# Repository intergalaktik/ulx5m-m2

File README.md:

# Work in progress!!! 

# ULX5M-M2
GateMate FPGA on M2 card

## Blinky

## SerDes test 

For initial test of V0.1 SerDes We have used messy setup.
On CM5 BaseBoard we have our ULX5M-GS board, and on M2 HAT we have M2 v0.1 board
PCIe lines are connected with small cable.
We have successfull data transfer and 1.25Gbit/s is without errors
2.5G is with some filter adjustment (v0.2) in good shape - almost without errors so usable!
We did not manage to get higher that 2.5G connections between v005 GS and M2 v0.1

#### ULX5M-M2 V001

- [x] JTAG 
- [x] FLASH
- [x] LEDs
- [x] Blinkey
- [x] USB - device shows up
- [] BTNS
- [] SDRAM
- [x] SerDes with connection to ULX5M-GS - low speed 1.25Gbit/s SerDes transfer.
- [] PCIe

#### ULX5M-M2 V002 - ordered

- [] JTAG 
- [] FLASH
- [] LEDs
- [] Blinkey
- [] USB - device shows up
- [] BTNS
- [] SDRAM
- [] SerDes with connection to ULX5M-GS I am getting low speed SerDes transfer.
- [] PCIe

## References

https://github.com/intergalaktik/ulx5m-gs

https://github.com/OLIMEX/GateMateA1-EVB

https://github.com/intergalaktik/Extension_Boards_for_Olimex_GateMate

https://github.com/YosysHQ/prjpeppercorn-test-cases

https://github.com/YosysHQ/prjpeppercorn
  
https://github.com/chili-chips-ba/openCologne

https://www.chili-chips.xyz/open-cologne

## Acknowledgements

This project was done in collaboration with Chili Chips*Ba team. 
They have put enormes effort in making all cores to work on GateMate even before we have our own board!
Thanks to them now we have big set of cores that can be used to check and improve opensource toolchain!
They are proven to be reliable partners that solves problem quickly and on side works on educating younger generations!
Also big thanks goes to YosysHQ as they are doing miracles with open source tooling, and we now finaly have one that works for GateMate!
From YosysHQ special thanks to Micko and Lofty that are helping in real time on Discord!
Special thanks to Patrick from Cologne, as without him and rest of Cologne team we would not be able to get this project done.

## Work on this board is financed by NLnet foundation

https://nlnet.nl/project/openCologne/

https://nlnet.nl/project/OpenCologne-PCIe/

https://github.com/chili-chips-ba/openCologne-PCIE

This project was funded through the NGI0 Commons Fund, a fund established by NLnet with financial support from the European Commission's Next Generation Internet programme, under the aegis of DG Communications Networks, Content and Technology under grant agreement No 101135429. Additional funding is made available by the Swiss State Secretariat for Education, Research and Innovation (SERI).

## Check up our blogposts
Comming soon!!!

## Contact us

Discord: https://discord.gg/qwMUk6W

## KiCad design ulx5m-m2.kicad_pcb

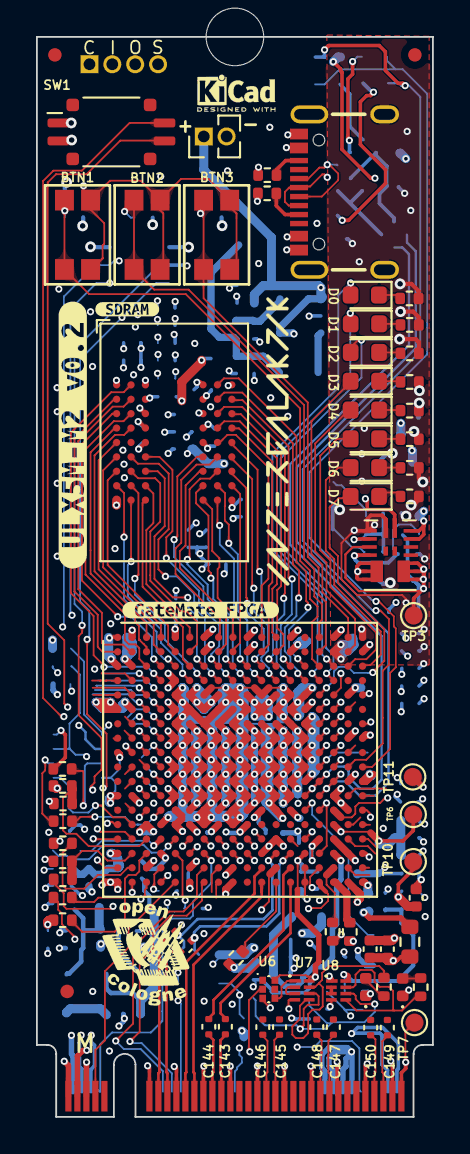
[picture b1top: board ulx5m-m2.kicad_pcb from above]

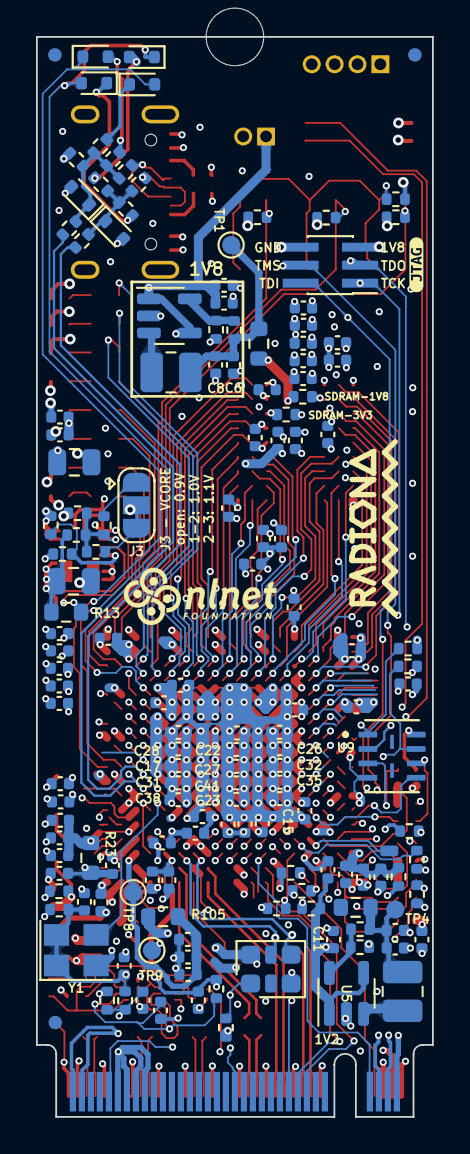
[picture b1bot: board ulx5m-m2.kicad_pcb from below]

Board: 6 copper layers, 22.0 x 60.0 mm, 231 parts (156 on the bottom side), 157 nets.

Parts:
BTN1, BTN2, BTN3: SW_Push; Switch_EVPAA
C1, C10: 22u; C_0805_2012Metric
C2, C11: 4u7; C_0402_1005Metric
C4, C15, C18, C23, C28, C32, C35, C38, C41, C126: 10n; C_0402_1005Metric
C6, C24: 10u; C_0402_1005Metric
C8, C29: 1u; C_0402_1005Metric
C13, C16, C21, C26, C36, C44, C51, C54, C75, C78, C86, C90, C94, C100, C122, C123, C131: 2u2; C_0402_1005Metric
C14, C17, C22, C27, C31, C34, C37, C40, C42, C45, C47, C48, C49, C52, C55, C56, C57, C76, C79, C80, C88, C89, C92, C93, C96, C97, C102, C103, C127, C128, C132, C133, C138: 100n; C_0402_1005Metric
C33, C87, C91, C95, C120, C121: 220n; C_0402_1005Metric
C39, C43, C50, C53, C58, C77, C98, C124, C125: 22u; C_0402_1005Metric
C85: 2.2uF; C_0402_1005Metric
C99, C101, C140, C141: 22nF; C_0402_1005Metric
C136, C137: 100n; C_0402_SI_M
C143, C144, C145, C146, C147, C148, C149, C150: 220nF; C_0402_SI_M
D1: green; D_0402_1005Metric
D2: red; D_0402_1005Metric
D3, D4: 3.6V; D_SOD-523
D5, D6, D7, D8: 1N914; D_SOD-523
D9, D10, D11, D12, D13, D14, D15, D16: LED; LED_0603_1608Metric
FID101, FID102, FID103, FID104, FID105, FID106: Fiducial; Fiducial_0.75mm_Mask1.5mm
H5: MountingHole_Pad; MountingHole_3.2mm_M3
J3: Vcore_sel; SolderJumper-3_P1.3mm_Open_RoundedPad1.0x1.5mm
J4: JTAG; PinHeader_2x03_P1.00mm_Vertical_SMD
J5: USB_C_Receptacle; USB-C_16
J10: M.2 M Key Connector
J101: JTAG_EXT; PinHeader_1x04_P1.27mm_Vertical
J102: 3V3_PSU; PinHeader_1x02_P1.27mm_Vertical
L1, L3: DFE322512F-2R2M=P2; L_1008_2520Metric
LoGo_opencologne: MountingHole; open_cologne_small
R1, R4, R143: 100k; R_0402_1005Metric
R2: 51k; R_0402_1005Metric
R3, R17, R18: 200k; R_0402_1005Metric
R7, R8, R116, R141, R142: 0R; R_0402_1005Metric
R9, R66, R112, R113, R115: dnp; R_0402_1005Metric
R10, R13, R21: 0R; R_0603_1608Metric
R12: 40k; R_0402_1005Metric
R14: 120k; R_0402_1005Metric
R15: 20k; R_0402_1005Metric
R16: 60k; R_0402_1005Metric
R23, R105, R106: 1R; R_0603_1608Metric
R24, R25, R27, R29, R30, R111: 10k; R_0402_1005Metric
R31, R32: 200R; R_0402_1005Metric
R33, R34, R35, R36, R38, R39: 4k7; R_0402_1005Metric
R37, R40, R41, R42, R43: 27R; R_0402_1005Metric
R44, R45: 27; R_0402_1005Metric
R46, R48, R58: 1k; R_0402_1005Metric
R47, R55: 12k1; R_0402_1005Metric
R59, R63, R64, R65, R86, R87, R88, R95, R118: R300; R_0402_1005Metric
R61, R62: 5k1; R_0402_1005Metric
R109: 200; R_0402_1005Metric
R121, R122, R123: 4R7; R_0402_1005Metric
R144, R145, R146: 1K; R_0402_1005Metric
SW1: 219-2MST; SW_DIP_SPSTx02_Slide_Copal_CVS-02xB_W5.9mm_P1mm
TP1: 1V8; TestPoint_Pad_D1.0mm
TP3: Vcore; TestPoint_Pad_D1.0mm
TP4: 1V2; TestPoint_Pad_D1.0mm
TP6: VDD_PLL; TestPoint_Pad_D1.0mm
TP7, TP9, TP11: GND; TestPoint_Pad_D1.0mm
TP8: VDD_SER_PLL; TestPoint_Pad_D1.0mm
TP10: VDD_SER; TestPoint_Pad_D1.0mm
TP12: SPI_FWD; TestPoint_Pad_1.0x1.0mm
U1, U5: TLV62569DBV; SOT-23-5
U3: MPM3833CGRH-Z
U4: GateMate-CCGM1A1; BGA-324_15.0x15.0mm_Layout18x18_P0.8mm_Ball0.45mm_Pad0.4mm_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
U6: 74LVC1G04GM,115; PESD3V3L5UF115
U7, U8: 74LVC2G00HK3-7; 74LVC2G00HK37
U9: AT25QL321-MBUE-T; SON80P400X300X60-10N
U10: IS42S16320D-6BLI
X2: 511FCA100M000BAG; Oscillator_SMD_SiTime_PQFD-6L_3.2x2.5mm
Y1: ASE2-25.000MHZ-L-C-T; Crystal_SMD_TXC_7M-4Pin_3.2x2.5mm
kibuzzard-6A9AE930: G***; kibuzzard-6A9AE930
kibuzzard-686AA7AF: G***; kibuzzard-686AA7AF
kibuzzard-686AA726: G***; kibuzzard-686AA726
kibuzzard-686CE423: G***; kibuzzard-686CE423
radiona: radiona

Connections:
+3V3: C1.1, C2.1, C11.1, C49.1, C85.1, C94.1, C95.1, C96.1, C97.1, C98.1, C99.1, C100.1, C101.1, C102.1, C103.1, C140.1, C141.1, J10.2 (+3.3V), J10.4 (+3.3V), J10.12 (+3.3V), J10.14 (+3.3V), J10.16 (+3.3V), J10.18 (+3.3V), J10.70 (+3.3V), J10.72 (+3.3V), J10.74 (+3.3V), J102.1, R1.1, R58.2, R115.2, R121.1, U1.1 (EN), U1.4 (VIN), U3.13 (IN), U3.14 (IN), U4.A16 (VDD_EB), U4.B18 (VDD_EB), U4.E14 (VDD_EB), U4.E17 (VDD_EB), U4.F13 (VDD_EB), U4.G14 (VDD_EA), U4.H17 (VDD_EA), U4.J14 (VDD_EA), U4.L14 (VDD_EA), U4.L17 (VDD_EA), U5.1 (EN), U5.4 (VIN)
/CLKREQ#: J10.52 (CLKREQ#), U4.V7 (IO_SA_B3)
/DEVSLP: J10.38 (DEVSLP), U4.R7 (IO_SA_A2)
/LED1#: J10.10 (DAS/DSS#/LED1#), U4.T6 (IO_SA_B1)
/M.2 M Key/PCIe_CLK_N: C137.2, J10.53 (REFCLKn)
/M.2 M Key/PCIe_CLK_P: C136.2, J10.55 (REFCLKp)
/M.2 M Key/PCIe_RX_N: J10.47 (PERn0/SATA-A-), U4.V11 (SER_RX_N)
/M.2 M Key/PCIe_RX_P: J10.49 (PERp0/SATA-A+), U4.U11 (SER_RX_P)
/M.2 M Key/PCIe_TX_N: C143.2, U4.V13 (SER_TX_N)
/M.2 M Key/PCIe_TX_P: C144.2, U4.U13 (SER_TX_P)
/M.2 M Key/PET0N: C143.1, J10.41 (PETn0/SATA-B+)
/M.2 M Key/PET0P: C144.1, J10.43 (PETp0/SATA-B-)
/M.2 M Key/PET1N: C145.1, J10.29 (PETn1)
/M.2 M Key/PET1P: C146.1, J10.31 (PETp1)
/M.2 M Key/PET2N: C147.1, J10.17 (PETn2)
/M.2 M Key/PET2P: C148.1, J10.19 (PETp2)
/M.2 M Key/PET3N: C149.1, J10.5 (PETn3)
/M.2 M Key/PET3P: C150.1, J10.7 (PETp3)
/PEDET: J10.69 (PEDET), U4.V5 (IO_SA_B0)
/PERST#: J10.50 (PERST#), U4.R6 (IO_SA_A1)
/PEWAKE#: J10.54 (PEWAKE#), U4.U7 (IO_SA_A3)
/SUSCLK: J10.68 (SUSCLK), U4.T7 (IO_SA_B2)
/config/+1V8_FLASH: C43.1, C44.1, C45.1, R123.1, U4.N5 (VDD_WA), U4.P3 (VDD_WA), U4.P5 (VDD_WA), U4.T1 (VDD_WA), U4.U3 (VDD_WA)
/config/CFG_DONE: U4.V3 (IO_WA_B2/CFG_DONE), U6.2 (A)
/config/JTAG_CFG_MD0: R29.1, U4.R5 (CFG_MD0/IO_WA_A0)
/config/JTAG_CFG_MD1: R27.1, U4.T5 (CFG_MD1/IO_WA_B0)
/config/JTAG_CFG_MD2: R25.1, SW1.4, U4.U4 (CFG_MD2/IO_WA_A1)
/config/JTAG_CFG_MD3: R24.1, SW1.3, U4.V4 (CFG_MD3/IO_WA_B1)
/config/JTAG_POR: R30.1, R66.2, U4.U1 (POR_EN/IO_WA_A3)
/config/JTAG_TCK: R39.1, R40.1, U4.R3 (JTAG_TCK/IO_WA_A5)
/config/JTAG_TDI: R36.2, R41.1, U4.T2 (JTAG_TDI/IO_WA_A4)
/config/JTAG_TDO: R42.1, U4.U2 (JTAG_TDO/IO_WA_B3)
/config/JTAG_TMS: R34.2, R43.1, U4.T3 (JTAG_TMS/IO_WA_B4)
/config/SPI_CSN: R38.2, U4.N3 (IO_WA_A8/~SPI_CS), U9.1 (~CS)
/config/SPI_IO0: U4.P2 (IO_WA_B7/SPI_D0), U9.5 (SI/SIO0)
/config/SPI_IO1: U4.P1 (IO_WA_A7/SPI_D1), U9.2 (SO/SIO1)
/config/SPI_IO2: R35.2, U4.R2 (IO_WA_B6/SPI_D2), U9.3 (~WP/SIO2)
/config/SPI_IO3: R33.2, U4.R1 (IO_WA_A6/SPI_D3), U9.7 (~RESET/SIO3)
/config/SPI_SCK: R37.1, U4.N4 (IO_WA_B8/SPI_CLK)
/config/~CFG_FAIL: U4.V2 (IO_WA_A2/~CFG_FAILED), U8.1 (1A)
/ethernet/ALED0: D9.1 (K), R59.1
/ethernet/ALED1: D10.1 (K), R63.1
/ethernet/ALED2: D11.1 (K), R64.1
/ethernet/ALED3: D12.1 (K), R65.1
/ethernet/ALED4: D13.1 (K), R86.1
/ethernet/ALED5: D14.1 (K), R87.1
/ethernet/ALED6: D15.1 (K), R88.1
/ethernet/ALED7: D16.1 (K), R95.1
/ethernet/BTN1: BTN1.2, R144.2, U4.C15 (IO_EB_B7)
/ethernet/BTN2: BTN2.2, R145.2, U4.A15 (IO_EB_B8)
/ethernet/BTN3: BTN3.2, R146.2, U4.B15 (IO_EB_A8)
/ethernet/FPD1+: J5.A6 (D+), J5.B6 (D+), R45.2
/ethernet/FPD1-: J5.A7 (D-), J5.B7 (D-), R44.2
/ethernet/LED0: D9.2 (A), U4.D15 (IO_EB_A7)
/ethernet/LED1: D10.2 (A), U4.C16 (IO_EB_B6)
/ethernet/LED2: D11.2 (A), U4.D16 (IO_EB_A6)
/ethernet/LED3: D12.2 (A), U4.A17 (IO_EB_B5)
/ethernet/LED4: D13.2 (A), U4.B17 (IO_EB_A5)
/ethernet/LED5: D14.2 (A), U4.C17 (IO_EB_B4)
/ethernet/LED6: D15.2 (A), U4.C18 (IO_EB_A4)
/ethernet/LED7: D16.2 (A), U4.E15 (IO_EB_B3)
/ethernet/USB25_N: R141.1, U4.L15 (IO_EA_B1), U4.M14 (IO_EA_B0)
/ethernet/USB25_P: R142.1, U4.L16 (IO_EA_A1), U4.M15 (IO_EA_A0)
/ethernet/USB_CC1: J5.A5 (CC1), R61.2
/ethernet/USB_CC2: J5.B5 (CC2), R62.2
/ethernet/USB_N: D4.1 (K), R44.1, R48.1, R55.2, R141.2
/ethernet/USB_P: D3.1 (K), R45.1, R46.2, R47.2, R58.1, R142.2
/ethernet/USB_PULL_N: D7.2 (A), D8.1 (K), U4.K17 (IO_EA_B2)
/ethernet/USB_PULL_P: D5.2 (A), D6.1 (K), U4.K18 (IO_EA_A2)
/lvds/+1V8_SB: C53.1, C54.1, C55.1, R122.1, U4.N11 (VDD_SB), U4.N13 (VDD_SB), U4.N18 (VDD_SB), U4.R15 (VDD_SB), U4.T18 (VDD_SB)
/lvds/+3V3_SA: C50.1, C51.1, C52.1, R121.2, U4.P6 (VDD_SA), U4.P8 (VDD_SA), U4.P10 (VDD_SA), U4.U6 (VDD_SA), U4.U9 (VDD_SA)
/lvds/CLK_25MHz: U4.N14 (CLK0/IO_SB_A8), Y1.3
/serdes/SER_CK_N: C137.1, U4.T13 (SER_CLK_N), X2.5 (OUT-)
/serdes/SER_CK_P: C136.1, U4.T12 (SER_CLK), X2.4 (OUT+)
/serdes/SER_PORT_ADJ: C133.1, R112.2, R113.1, U4.V15 (POR_ADJ)
GND: C1.2, C2.2, C4.1, C6.2, C8.2, C10.2, C11.2, C13.2, C14.2, C15.2, C16.2, C17.2, C18.2, C21.2, C22.2, C23.2, C24.2, C26.2, C27.2, C28.2, C29.2, C31.2, C32.2, C33.2, C34.2, C35.2, C36.2, C37.2, C38.2, C39.2, C40.2, C41.2, C42.2, C43.2, C44.2, C45.2, C47.2, C48.2, C49.2, C50.2, C51.2, C52.2, C53.2, C54.2, C55.2, C56.2, C57.2, C58.2, C75.2, C76.2, C77.2, C78.2, C79.2, C80.2, C85.2, C86.2, C87.2, C88.2, C89.2, C90.2, C91.2, C92.2, C93.2, C94.2, C95.2, C96.2, C97.2, C98.2, C99.2, C100.2, C101.2, C102.2, C103.2, C120.2, C121.2, C122.2, C123.2, C124.2, C125.2, C126.2, C127.2, C128.2, C131.2, C132.2, C133.2, C138.2, C140.2, C141.2, D1.1 (K), D2.1 (K), D3.2 (A), D4.2 (A), J3.2, J4.6, J5.GND, J5.NC1 (NC), J5.NC2 (NC), J5.NC3 (NC), J5.S (SHIELD), J10.1 (GND), J10.3 (GND), J10.9 (GND), J10.15 (GND), J10.21 (GND), J10.27 (GND), J10.33 (GND), J10.39 (GND), J10.45 (GND), J10.51 (GND), J10.57 (GND), J10.71 (GND), J10.73 (GND), J10.75 (GND), J102.2, R2.2, R4.2, R7.2, R8.2, R12.1, R18.2, R24.2, R25.2, R27.2, R29.2, R30.2, R39.2, R59.2, R61.1, R62.1, R63.2, R64.2, R65.2, R86.2, R87.2, R88.2, R95.2, R109.1, R113.2, R118.2, TP7.1 (1_1), TP9.1 (1_1), TP11.1 (1_1), U1.2 (GND), U3.1 (AGND), U3.16 (PGND), U4.A1 (GND), U4.A7 (GND), U4.A10 (GND), U4.A13 (GND), U4.A18 (GND), U4.B16 (GND), U4.C1 (GND), U4.E5 (GND), U4.E7 (GND), U4.E9 (GND), U4.E11 (GND), U4.E13 (GND), U4.E18 (GND), U4.F1 (GND), U4.F6 (GND), U4.F8 (GND), U4.F10 (GND), U4.F12 (GND), U4.F14 (GND), U4.G5 (GND), U4.G7 (GND), U4.G9 (GND), U4.G11 (GND), U4.G13 (GND), U4.H6 (GND), U4.H8 (GND), U4.H10 (GND), U4.H12 (GND), U4.H14 (GND), U4.H18 (GND), U4.J1 (GND), U4.J5 (GND), U4.J7 (GND), U4.J9 (GND), U4.J11 (GND), U4.J13 (GND), U4.K6 (GND), U4.K8 (GND), U4.K10 (GND), U4.K12 (GND), U4.K14 (GND), U4.L5 (GND), U4.L7 (GND), U4.L9 (GND), U4.L11 (GND), U4.L13 (GND), U4.L18 (GND), U4.M1 (GND), U4.M6 (GND), U4.M8 (GND), U4.M10 (GND), U4.M12 (GND), U4.M16 (GND), U4.N7 (GND), U4.N9 (GND), U4.N12 (GND), U4.N17 (GND), U4.P4 (GND), U4.P7 (GND), U4.P9 (GND), U4.R12 (GND), U4.R16 (GND), U4.T4 (GND), U4.T11 (GND), U4.T17 (GND), U4.U14 (GND), U4.U15 (GND), U4.V1 (GND), U4.V6 (GND), U4.V9 (GND), U4.V14 (GND), U4.V18 (GND), U5.2 (GND), U6.3 (GND), U7.4 (GND), U8.4 (GND), U9.4 (GND), U10.A1 (VSS), U10.A3 (VSSQ), U10.B7 (VSSQ), U10.C3 (VSSQ), U10.D7 (VSSQ), U10.E3 (VSS), U10.J1 (VSS), X2.3 (GND), Y1.2
unnamed: BTN1.1, BTN2.1, BTN3.1, R118.1
unnamed: C6.1, C8.1, L1.2, R3.1, R10.1, TP1.1 (1_1)
unnamed: C24.1, C29.1, L3.2, R17.1, R21.1, TP4.1 (1_1)
unnamed: D1.2 (A), R31.2
unnamed: D2.2 (A), R32.2
unnamed: D5.1 (K), R46.1
unnamed: D6.2 (A), R47.1
unnamed: D7.1 (K), R48.2
unnamed: D8.2 (A), R55.1
unnamed: J3.1, R14.1
unnamed: J3.3, R16.1
unnamed: J4.1, J101.1, R40.2
unnamed: J4.2, J101.2, R41.2
unnamed: J4.3, J101.3, R42.2
unnamed: J4.4, J101.4, R43.2
unnamed: R7.1, U4.U16 (GND)
unnamed: R8.1, U4.V16 (GND)
unnamed: R3.2, R4.1, U1.5 (FB)
unnamed: L1.1, U1.3 (SW)
unnamed: R1.2, R2.1, U3.4 (EN)
unnamed: R12.2, R14.2, R15.2, R16.2, U3.2 (FB)
unnamed: C10.1, R13.1, R15.1, TP3.1 (1_1), U3.3 (OUT_S), U3.8 (OUT), U3.9 (OUT), U3.10 (OUT)
unnamed: U3.5 (SW), U3.6 (SW), U3.7 (SW), U3.15 (SW)
unnamed: R109.2, U4.V12 (SER_RTERM)
unnamed: TP12.1 (1_1), U4.R4 (IO_WA_B5/SPI_FWD)
unnamed: R9.1, U4.N16 (NC)
unnamed: R17.2, R18.1, U5.5 (FB)
unnamed: L3.1, U5.3 (SW)
unnamed: U6.4 (Y), U7.1 (1A)
unnamed: U7.2 (1B), U7.3 (2Y)
unnamed: R31.1, U7.5 (2A), U7.7 (1Y)
unnamed: U8.2 (1B), U8.3 (2Y)
unnamed: R32.1, U8.5 (2A), U8.7 (1Y)
unnamed: R37.2, U9.6 (SCLK)
unnamed: R143.2, X2.1 (OE)
RST_N: C138.1, R111.2, U4.N15 (IO_SB_B8), U4.T15 (RST_N), U7.6 (2B), U8.6 (2B)
SDRAM_A0: U4.D10 (IO_NB_A1), U10.H7 (A0)
SDRAM_A1: U4.D11 (IO_NB_A3), U10.H8 (A1)
SDRAM_A2: U4.C10 (IO_NB_B1), U10.J8 (A2)
SDRAM_A3: U4.A9 (IO_NB_B0), U10.J7 (A3)
SDRAM_A4: U4.C6 (IO_NA_A3), U10.J3 (A4)
SDRAM_A5: U4.D6 (IO_NA_B3), U10.J2 (A5)
SDRAM_A6: U4.A6 (IO_NA_A4), U10.H3 (A6)
SDRAM_A7: U4.D7 (IO_NA_B5), U10.H2 (A7)
SDRAM_A8: U4.C5 (IO_NA_B2), U10.H1 (A8)
SDRAM_A9: U4.C7 (IO_NA_A5), U10.G3 (A9)
SDRAM_A10: U4.B9 (IO_NB_A0), U10.H9 (A10)
SDRAM_A11: U4.B6 (IO_NA_B4), U10.G2 (A11)
SDRAM_A12: U4.B5 (IO_NA_A2), U10.G1 (A12)
SDRAM_BA0: U4.B8 (IO_NA_B7), U10.G7 (BA0)
SDRAM_BA1: U4.C9 (IO_NA_A8), U10.G8 (BA1)
SDRAM_CKE: U4.C8 (IO_NA_A6), U10.F3 (CKE)
SDRAM_CLK: U4.D8 (IO_NA_B6), U10.F2 (CLK)
SDRAM_D0: U4.C14 (IO_NB_B8), U10.A8 (DQ0)
SDRAM_D1: U4.C13 (IO_NB_B6), U10.B9 (DQ1)
SDRAM_D2: U4.D14 (IO_NB_A8), U10.B8 (DQ2)
SDRAM_D3: U4.B12 (IO_NB_A4), U10.C9 (DQ3)
SDRAM_D4: U4.D13 (IO_NB_A6), U10.C8 (DQ4)
SDRAM_D5: U4.B11 (IO_NB_A2), U10.D9 (DQ5)
SDRAM_D6: U4.A12 (IO_NB_B4), U10.D8 (DQ6)
SDRAM_D7: U4.C12 (IO_NB_B5), U10.E9 (DQ7)
SDRAM_D8: U4.B4 (IO_NA_B1), U10.E1 (DQ8)
SDRAM_D9: U4.A3 (IO_NA_A0), U10.D2 (DQ9)
SDRAM_D10: U4.B3 (IO_NA_B0), U10.D1 (DQ10)
SDRAM_D11: U4.C3 (IO_WC_A7), U10.C2 (DQ11)
SDRAM_D12: U4.C4 (IO_WC_B7), U10.C1 (DQ12)
SDRAM_D13: U4.B2 (IO_WC_B8), U10.B2 (DQ13)
SDRAM_D14: U4.B1 (IO_WC_A8), U10.B1 (DQ14)
SDRAM_D15: U4.D4 (IO_WC_B6), U10.A2 (DQ15)
SDRAM_DQM0: U4.A11 (IO_NB_B2), U10.E8 (DQML)
SDRAM_DQM1: U4.A4 (IO_NA_A1), U10.F1 (DQMH)
SDRAM_VCC: C57.1, C58.1, C75.1, C76.1, C77.1, C78.1, C79.1, C80.1, C86.1, C87.1, C88.1, C89.1, C90.1, C91.1, C92.1, C93.1, R115.1, R116.1, U4.A2 (VDD_WC), U4.A5 (VDD_NA), U4.B7 (VDD_NA), U4.B10 (VDD_NB), U4.B13 (VDD_NB), U4.C2 (VDD_WC), U4.D5 (VDD_WC), U4.E6 (VDD_NA), U4.E8 (VDD_NA), U4.E10 (VDD_NB), U4.E12 (VDD_NB), U4.F2 (VDD_WC), U4.F5 (VDD_WC), U4.F7 (VDD_NA), U4.F11 (VDD_NB), U4.H5 (VDD_WB), U4.J2 (VDD_WB), U4.K5 (VDD_WB), U4.M2 (VDD_WB), U4.M5 (VDD_WB), U10.A7 (VDDQ), U10.A9 (VDD), U10.B3 (VDDQ), U10.C7 (VDDQ), U10.D3 (VDDQ), U10.E7 (VDD), U10.J9 (VDD)
SDRAM_nCAS: U4.D9 (IO_NA_B8), U10.F7 (~CAS)
SDRAM_nCS: U4.C11 (IO_NB_B3), U10.G9 (~CS)
SDRAM_nRAS: U4.A8 (IO_NA_A7), U10.F8 (~RAS)
SDRAM_nWE: U4.D12 (IO_NB_A5), U10.F9 (~WE)
VDD_CLK: C4.2, C47.1, C48.1, C56.1, C126.1, C131.1, C132.1, J4.5, R10.2, R33.1, R34.1, R35.1, R36.1, R38.1, R66.1, R111.1, R112.1, R116.2, R122.2, R123.2, R143.1, R144.1, R145.1, R146.1, SW1.1, SW1.2, U4.T14 (VDD_CLK), U6.6 (VCC), U7.8 (VCC), U8.8 (VCC), U9.8 (VCC), X2.6 (VDD), Y1.1, Y1.4
VDD_CORE: C13.1, C14.1, C15.1, C16.1, C17.1, C18.1, C21.1, C22.1, C23.1, C26.1, C27.1, C28.1, C31.1, C32.1, C34.1, C35.1, C37.1, C38.1, C40.1, C41.1, C42.1, C127.1, C128.1, R13.2, R23.1, R105.1, R106.1, U4.F9 (VDD), U4.G6 (VDD), U4.G8 (VDD), U4.G10 (VDD), U4.G12 (VDD), U4.H7 (VDD), U4.H9 (VDD), U4.H11 (VDD), U4.H13 (VDD), U4.J6 (VDD), U4.J8 (VDD), U4.J10 (VDD), U4.J12 (VDD), U4.K7 (VDD), U4.K9 (VDD), U4.K11 (VDD), U4.K13 (VDD), U4.L6 (VDD), U4.L8 (VDD), U4.L10 (VDD), U4.L12 (VDD), U4.M7 (VDD), U4.M9 (VDD), U4.M11 (VDD), U4.M13 (VDD), U4.N6 (VDD), U4.N8 (VDD), U4.N10 (VDD)
VDD_PLL: C33.1, C36.1, C39.1, R23.2, TP6.1 (1_1), U4.P16 (VDD_PLL)
VDD_SER: C121.1, C123.1, C125.1, R9.2, R106.2, TP10.1 (1_1), U4.U12 (VDD_SER), U4.V17 (VDD_SER)
VDD_SER_PLL: C120.1, C122.1, C124.1, R105.2, TP8.1 (1_1), U4.T16 (VDD_SER_PLL)

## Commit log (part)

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2026-04-13 Adding M2
2026-04-13 cleanup
2026-06-03 Version 1.0
2026-06-03 Cleanup for v2 - we need to remove all modules, rotate FPGA, then assemble them together
2026-06-03 Chaning place of SDRAM
2026-06-23 Adding pictures to main
2026-06-23 README update

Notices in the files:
parts and their libraries:
project_license: CERN-OHL-S v2
